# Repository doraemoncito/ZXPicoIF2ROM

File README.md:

# ZXPicoIF2ROM
IF2 ROM Cartridge Replacement using a Raspberry Pico. Makes use of the PIO state machine of the Raspberry Pico which removes the need to overclock the PICO.

Based on the original design by Derek Fountain https://github.com/derekfountain/zx-spectrum-pico-rom. This GitHub has a lot of great detail on how this all works so recommend a read.

## Usage

Usage is very simple. On every cold boot the Spectrum will default to the first ROM in the `roms[]` array which is basically the ROMs in the `roms.h` header file. To change the ROM you simply press and hold (firmware v0.3+) the user button for >1second. Upon release the new ROM will boot. If you want to simply reset the Spectrum just press the user button and do not hold down. As of v0.4 there is also now a display which tells you which ROM is being loaded. Also if you hold down the user button it will cycle through the ROMs. I've uploaded a quick video to YouTube of it in action:

To add more ROMs or change the ones provided here simply add them to the header file. As of v0.4 firmware you need to compress the ROMs first before adding. The `compressrom` utility will do this for you, creating a header file which can simply be copied into the main `roms.h` file, make sure you keep `switchrom` in this header file which is needed for the main code. After adding to the `roms.h` file you need to update the `roms[]` arrray with the corect header name, add the display name you want to the `romname[]` array (max 32chars) and make sure the `MAXROMS` define is set to the correct number of ROMs available.

If you would like to try out different ROMs there are a lot on Paul Farrow's website http://www.fruitcake.plus.com/Sinclair/Interface2/Cartridges/Interface2_RC_Cartridges.htm

For demonstration purposes I have included the following ROMs:
- Original ZX Spectrum ROM (copyright Amstrad)
- Retroleum DiagROM v1.59 by Retroleum (http://blog.retroleum.co.uk/electronics-articles/a-diagnostic-rom-image-for-the-zx-spectrum/)
- ZX Spectrum Diagnostics v0.37 by Brendan Alford (https://github.com/brendanalford/zx-diagnostics/releases/tag/v0.37)
- ZX Spectrum Test Cartridge (copyright Amstrad)
- 128k RAM Tester by Paul Farrow (http://www.fruitcake.plus.com/Sinclair/Interface2/Cartridges/Interface2_RC_New_RAM_Tester.htm)
- Looking Glass ROM by Geoff Wearmouth as used on the Spectrum Next (https://gitlab.com/thesmog358/tbblue/-/tree/master/machines/next)

## Compressed ROMs

From firmware v0.4 I shifted to use compressed ROMs just to save a little space if you want to add a lot of ROMs. PICO flash is 2MB so space for ~100 ROMs, so not a massive issue but no need to waste space. I added a little utility `compressrom` which compresses a ROM binary file and creates the approprite header file to use with the main code. The utility will also pad 8kB ROMs to 16kB saving the need to do this manually.

## PIO & DMA

Derek's original design used one of the processors of the RP2040 to read the ADDRESS pins and write out the DATA lines if required. In order to do this fast enough the RP2040 needed to be overclocked. For my version I decided to use the [PIO](https://www.raspberrypi.com/news/what-is-pio/) mainly as I wanted to learn how to use it. The PIO has many advantages including being fast enough to avoid an overclock but also it works completely independently from the main CPU and is not affected by things like interrupts.

In order for the PIO to work it needs to be coupled with the PICOs DMA which will feed the PIO with the correct data to write to the DATA lines. I first saw how this could work from the 6502 example on [Rumbledethumps YouTube channel](https://www.youtube.com/watch?v=GOEI2OpMncY&t=374s) and adapted this to work on the ZX Spectrum. The idea is to set-up two DMA channels, one will get the memory address required from the PIO FIFO and use that to tell the second DMA channel what data to send back the PIO FIFO. The code included on this GitHub details how this works but to summarise:
1. PIO reads (IN) the 14 address pins (A0-A13) to the ISR
2. The ISR is auto pushed into the PIO FIFO
3. DMA channel 1 reads the PIO FIFO and puts this into the DMA channel 2 read address
4. DMA channel 2 sends the single byte of data (8bits) at the new read address to the PIO FIFO
5. PIO auto pushes the PIO FIFO to the OSR which is then outputted (OUT) to the data pins (D0-D7)
6. Wrap back to 1

The PIO allows for the set-up of independent input and output pins which fits perfectly for this use case. There are also a couple of additional set-up steps such as enabling auto-push on the PIO and converting the 14bit address read in to a 32bit address in PICO memory. This is all detailed in the code.

My initial design had the PIO wait for the correct signal before sending the data (WAIT statement on A14, RD, A15 & MREQ all being zero) but I determined that this was not need as it can be accomplished just using the output enable (OE) pin on the 74LS245 chip. This pin controls whether data is actually sent to the Spectrum or not so simply connecting this to the OR of MREQ, A14, A15 & RD means only when all 4 are 0 is any data sent. This is basically a ROM (0-16383bytes) Read (RD) Memory Request (MREQ). This allowed me to simplify the PIO code to just loop constantly reading the address and writing the data.

## Schematic

The main changes from Derek's original circuit was to put the Address & Data GPIOs in order which is required for the PIO code. I also removed the output from the OR chip to the PICO as I shifted to just controlling the data output using the OE pin as described above. This freed up a couple of GPIOs which I decided to allocate to an I2C connector just in case I wanted to attach a screen or something else.

## PCB

For the PCB design I moved the components to the reverse of the PCB meaning I could mount some components lower down, knowing they wouldn't clash with the case, thus giving more room. I also shifted to using through hole components instead of surface mount due to my soldering skills. I also added a RUN button which basically resets the PICO, useful for flashing new firmware or recovering the PICO if it crashes (which is never does).

v1.1 Gerbers are available in the file https://github.com/TomDDG/ZXPicoIF2ROM/blob/main/picoif2_2023-05-04.zip

I've also created a simple 3D Printed case for the PCB which you can find on Printables https://www.printables.com/model/479276-zxpicoif2rom-v11pcb-case

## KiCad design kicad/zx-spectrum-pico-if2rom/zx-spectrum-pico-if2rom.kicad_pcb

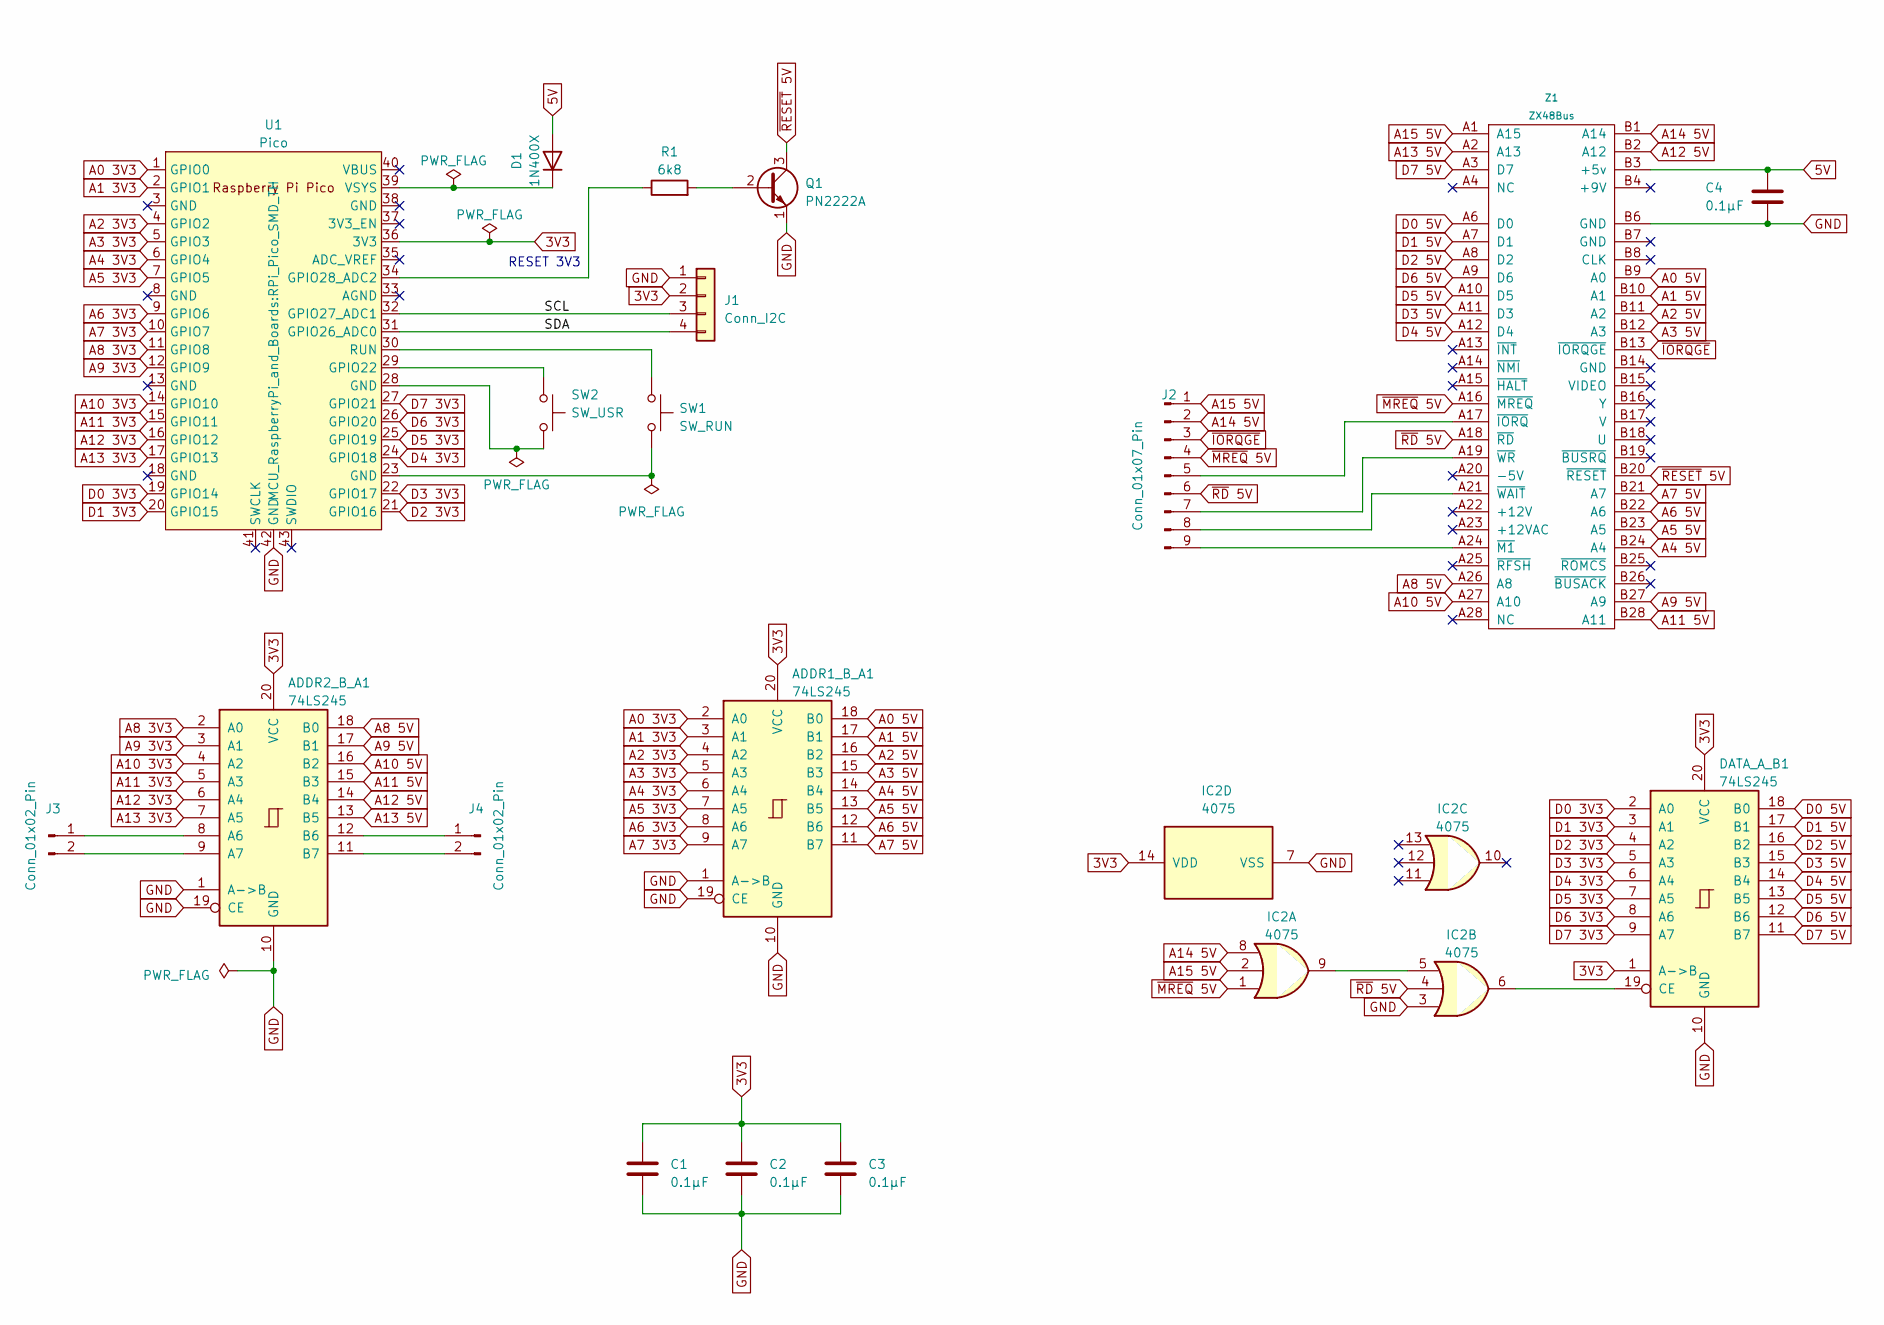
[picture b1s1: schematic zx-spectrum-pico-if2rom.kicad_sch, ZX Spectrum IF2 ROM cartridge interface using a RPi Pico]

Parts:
ADDR1_B_A1, ADDR2_B_A1: 74LS245; DIP-20_W7.62mm_Socket
C1, C2, C3, C4: 0.1µF; C_Axial_L3.8mm_D2.6mm_P7.50mm_Horizontal
D1: 1N400X; D_DO-41_SOD81_P10.16mm_Horizontal
DATA_A_B1: 74LS245; DIP-20_W7.62mm_Socket
IC2: 4075; DIP-14_W7.62mm_Socket
J1: Conn_I2C; PinHeader_1x04_P2.00mm_Vertical
J2: Conn_01x07_Pin; PinHeader_1x07_P2.00mm_Vertical
J3, J4: Conn_01x02_Pin; PinHeader_1x02_P2.00mm_Vertical
Q1: PN2222A; TO-92_Inline
R1: 6k8; R_Axial_DIN0204_L3.6mm_D1.6mm_P5.08mm_Horizontal
SW1: SW_RUN; SW_Tactile_Straight_KSA0Axx1LFTR
SW2: SW_USR; SW_Tactile_SPST_Angled_PTS645Vx58-2LFS
U1: Pico; RPi_Pico_SMD_TH
Z1: ZX48Bus; ZX_Bus_Pin_Header

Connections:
3V3: ADDR1_B_A1.20 (VCC), ADDR2_B_A1.20 (VCC), C1.1, C2.1, C3.1, DATA_A_B1.1 (A->B), DATA_A_B1.20 (VCC), IC2.14 (VDD), J1.2, U1.36 (3V3)
5V: C4.1, D1.2 (A), Z1.B3 (+5v)
/SCL: J1.3, U1.32 (GPIO27_ADC1)
/SDA: J1.4, U1.31 (GPIO26_ADC0)
A0 3V3: ADDR1_B_A1.2 (A0), U1.1 (GPIO0)
A0 5V: ADDR1_B_A1.18 (B0), Z1.B9 (A0)
A1 3V3: ADDR1_B_A1.3 (A1), U1.2 (GPIO1)
A1 5V: ADDR1_B_A1.17 (B1), Z1.B10 (A1)
A2 3V3: ADDR1_B_A1.4 (A2), U1.4 (GPIO2)
A2 5V: ADDR1_B_A1.16 (B2), Z1.B11 (A2)
A3 3V3: ADDR1_B_A1.5 (A3), U1.5 (GPIO3)
A3 5V: ADDR1_B_A1.15 (B3), Z1.B12 (A3)
A4 3V3: ADDR1_B_A1.6 (A4), U1.6 (GPIO4)
A4 5V: ADDR1_B_A1.14 (B4), Z1.B24 (A4)
A5 3V3: ADDR1_B_A1.7 (A5), U1.7 (GPIO5)
A5 5V: ADDR1_B_A1.13 (B5), Z1.B23 (A5)
A6 3V3: ADDR1_B_A1.8 (A6), U1.9 (GPIO6)
A6 5V: ADDR1_B_A1.12 (B6), Z1.B22 (A6)
A7 3V3: ADDR1_B_A1.9 (A7), U1.10 (GPIO7)
A7 5V: ADDR1_B_A1.11 (B7), Z1.B21 (A7)
A8 3V3: ADDR2_B_A1.2 (A0), U1.11 (GPIO8)
A8 5V: ADDR2_B_A1.18 (B0), Z1.A26 (A8)
A9 3V3: ADDR2_B_A1.3 (A1), U1.12 (GPIO9)
A9 5V: ADDR2_B_A1.17 (B1), Z1.B27 (A9)
A10 3V3: ADDR2_B_A1.4 (A2), U1.14 (GPIO10)
A10 5V: ADDR2_B_A1.16 (B2), Z1.A27 (A10)
A11 3V3: ADDR2_B_A1.5 (A3), U1.15 (GPIO11)
A11 5V: ADDR2_B_A1.15 (B3), Z1.B28 (A11)
A12 3V3: ADDR2_B_A1.6 (A4), U1.16 (GPIO12)
A12 5V: ADDR2_B_A1.14 (B4), Z1.B2 (A12)
A13 3V3: ADDR2_B_A1.7 (A5), U1.17 (GPIO13)
A13 5V: ADDR2_B_A1.13 (B5), Z1.A2 (A13)
A14 5V: IC2.8, J2.2, Z1.B1 (A14)
A15 5V: IC2.2, J2.1, Z1.A1 (A15)
D0 3V3: DATA_A_B1.2 (A0), U1.19 (GPIO14)
D0 5V: DATA_A_B1.18 (B0), Z1.A6 (D0)
D1 3V3: DATA_A_B1.3 (A1), U1.20 (GPIO15)
D1 5V: DATA_A_B1.17 (B1), Z1.A7 (D1)
D2 3V3: DATA_A_B1.4 (A2), U1.21 (GPIO16)
D2 5V: DATA_A_B1.16 (B2), Z1.A8 (D2)
D3 3V3: DATA_A_B1.5 (A3), U1.22 (GPIO17)
D3 5V: DATA_A_B1.15 (B3), Z1.A11 (D3)
D4 3V3: DATA_A_B1.6 (A4), U1.24 (GPIO18)
D4 5V: DATA_A_B1.14 (B4), Z1.A12 (D4)
D5 3V3: DATA_A_B1.7 (A5), U1.25 (GPIO19)
D5 5V: DATA_A_B1.13 (B5), Z1.A10 (D5)
D6 3V3: DATA_A_B1.8 (A6), U1.26 (GPIO20)
D6 5V: DATA_A_B1.12 (B6), Z1.A9 (D6)
D7 3V3: DATA_A_B1.9 (A7), U1.27 (GPIO21)
D7 5V: DATA_A_B1.11 (B7), Z1.A3 (D7)
GND: ADDR1_B_A1.1 (A->B), ADDR1_B_A1.10 (GND), ADDR1_B_A1.19 (CE), ADDR2_B_A1.1 (A->B), ADDR2_B_A1.10 (GND), ADDR2_B_A1.19 (CE), C1.2, C2.2, C3.2, C4.2, DATA_A_B1.10 (GND), IC2.3, IC2.7 (VSS), J1.1, Q1.1 (E), U1.42 (GND), Z1.B6 (GND)
unnamed: ADDR2_B_A1.8 (A6), J3.1
unnamed: ADDR2_B_A1.9 (A7), J3.2
unnamed: ADDR2_B_A1.12 (B6), J4.1
unnamed: ADDR2_B_A1.11 (B7), J4.2
unnamed: D1.1 (K), U1.39 (VSYS)
unnamed: DATA_A_B1.19 (CE), IC2.6
unnamed: IC2.5, IC2.9
unnamed: J2.5, Z1.A17 (~IORQ)
unnamed: J2.7, Z1.A19 (~WR)
unnamed: J2.8, Z1.A21 (~WAIT)
unnamed: J2.9, Z1.A24 (~M1)
unnamed: Q1.2 (B), R1.2
unnamed: SW1.2, U1.23 (GND)
unnamed: SW2.2, U1.28 (GND)
unnamed: SW2.1, U1.29 (GPIO22)
unnamed: R1.1, U1.34 (GPIO28_ADC2)
unnamed: SW1.1, U1.30 (RUN)
~IORQGE: J2.3, Z1.B13 (~IORQGE)
~MREQ 5V: IC2.1, J2.4, Z1.A16 (~MREQ)
~RD 5V: IC2.4, J2.6, Z1.A18 (~RD)
~RESET 5V: Q1.3 (C), Z1.B20 (~RESET)

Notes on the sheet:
RESET 3V3

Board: 2 copper layers, 19 parts (1 on the bottom side), 70 nets, no tracks yet.

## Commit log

2023-05-13 Added KiCad version of the circuit schematic and PCB
